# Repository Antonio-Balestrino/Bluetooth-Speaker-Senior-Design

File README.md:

Bluetooth Speaker Senior Design Project:
Welcome to the repository for our senior design group project focused on building a Bluetooth speaker! This project aims to create a portable and versatile Bluetooth speaker system with a focus on high-quality audio output and user-friendly features.

Project Overview:
Our project involves designing and constructing a Bluetooth speaker from scratch. We're incorporating various components including speakers, amplifiers, Bluetooth modules, microcontrollers, and power sources to create a fully functional and aesthetically pleasing speaker system.

Features:
* Bluetooth Connectivity: Seamlessly connect your devices and stream audio wirelessly to the speaker.
* High-Quality Audio: Delivering crisp and clear sound output for an immersive listening experience.
* User-Friendly Interface: Intuitive controls for easy operation, including volume adjustment and playback controls.

Contributors:
Antonio Balestrino​, Blake Chanhmisay​, Rogelio M Hernandez​, Faith Murray​, Tristan Storbeck​

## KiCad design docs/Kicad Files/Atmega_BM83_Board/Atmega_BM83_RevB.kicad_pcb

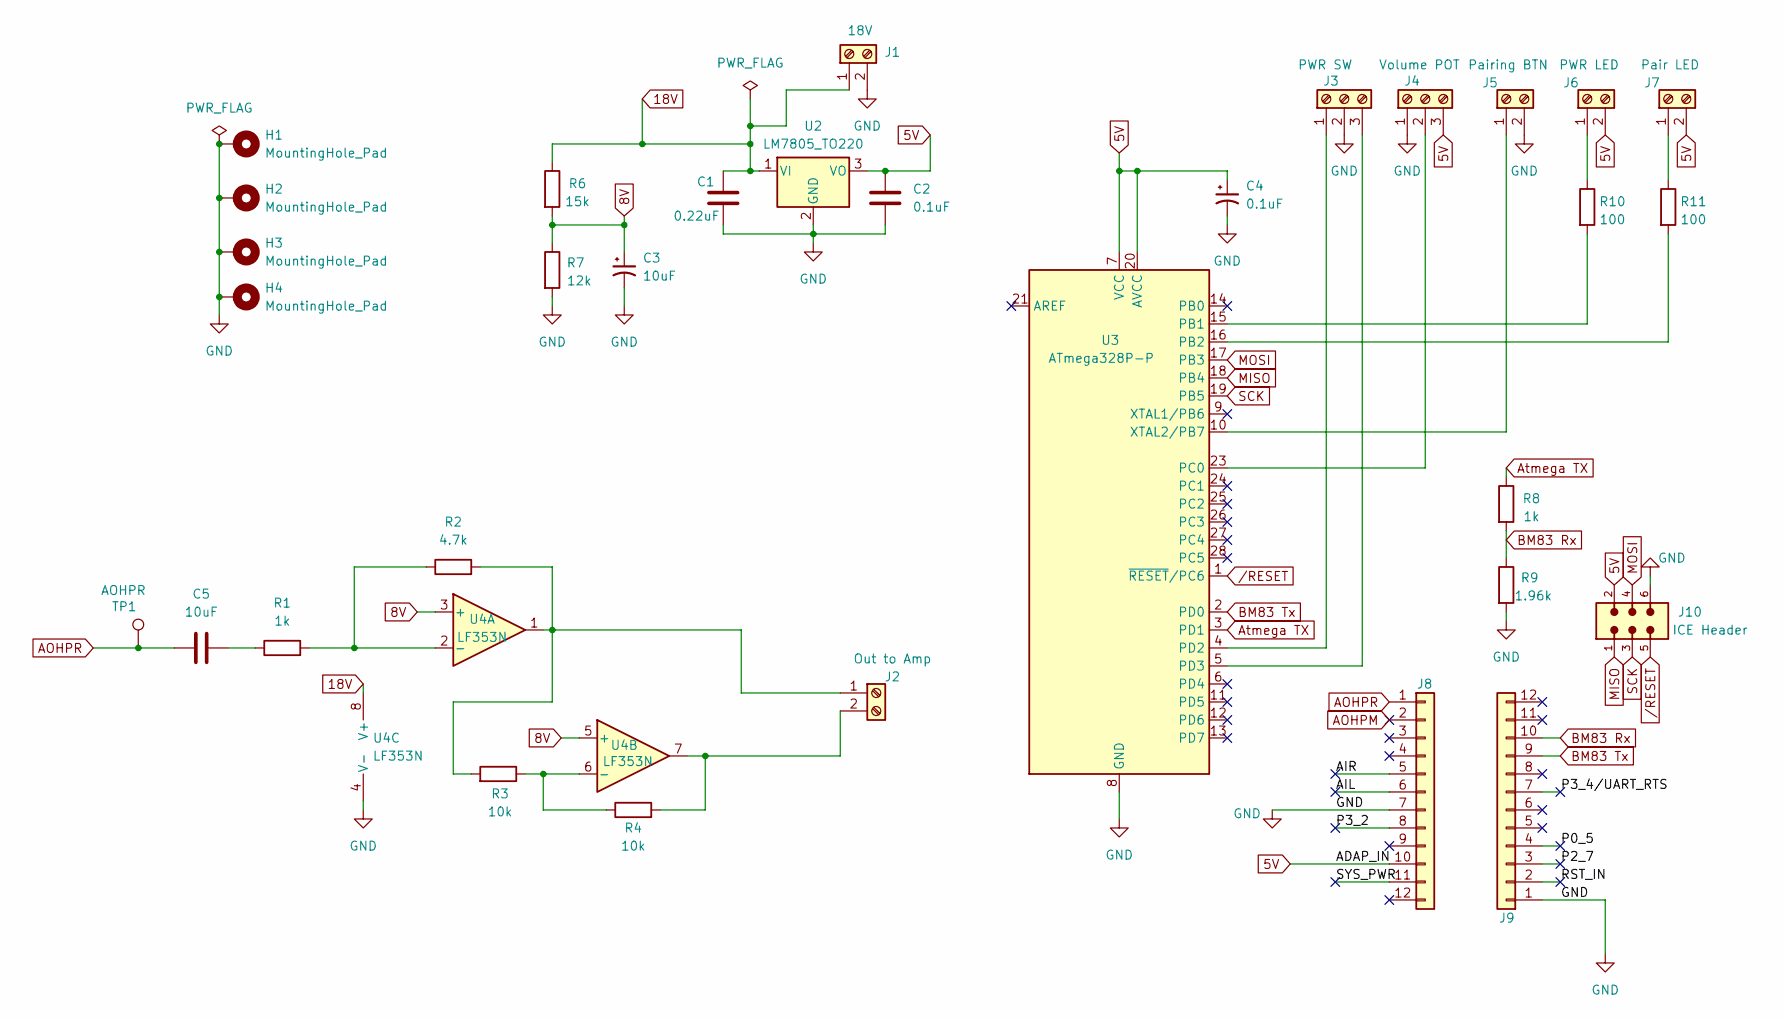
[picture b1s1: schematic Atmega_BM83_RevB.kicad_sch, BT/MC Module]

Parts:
C1: 0.22uF; C_Rect_L7.0mm_W3.5mm_P5.00mm
C2, C4: 0.1uF; C_Rect_L7.0mm_W2.5mm_P5.00mm
C3: 10uF; CP_Radial_Tantal_D5.0mm_P5.00mm
C5: 10uF; C_Disc_D6.0mm_W4.4mm_P5.00mm
H1, H2, H3, H4: MountingHole_Pad; MountingHole_3.5mm_Pad
J1: 18V; TerminalBlock_Phoenix_MKDS-1,5-2_1x02_P5.00mm_Horizontal
J2: Out to Amp; TerminalBlock_Phoenix_MKDS-1,5-2_1x02_P5.00mm_Horizontal
J3: PWR SW; TerminalBlock_Phoenix_MKDS-1,5-3_1x03_P5.00mm_Horizontal
J4: Volume POT; TerminalBlock_Phoenix_MKDS-1,5-3_1x03_P5.00mm_Horizontal
J5: Pairing BTN; TerminalBlock_Phoenix_MKDS-1,5-2_1x02_P5.00mm_Horizontal
J6: PWR LED; TerminalBlock_Phoenix_MKDS-1,5-2_1x02_P5.00mm_Horizontal
J7: Pair LED; TerminalBlock_Phoenix_MKDS-1,5-2_1x02_P5.00mm_Horizontal
J8, J9: Conn_01x12; PinHeader_1x12_P2.54mm_Vertical
J10: ICE Header; ICE_Header; PART-NUMBER 61200621621
R1, R8: 1k; R_Axial_DIN0207_L6.3mm_D2.5mm_P10.16mm_Horizontal
R2: 4.7k; R_Axial_DIN0207_L6.3mm_D2.5mm_P10.16mm_Horizontal
R3, R4: 10k; R_Axial_DIN0207_L6.3mm_D2.5mm_P10.16mm_Horizontal
R6: 15k; R_Axial_DIN0207_L6.3mm_D2.5mm_P10.16mm_Horizontal
R7: 12k; R_Axial_DIN0207_L6.3mm_D2.5mm_P10.16mm_Horizontal
R9: 1.96k; R_Axial_DIN0207_L6.3mm_D2.5mm_P10.16mm_Horizontal
R10, R11: 100; R_Axial_DIN0207_L6.3mm_D2.5mm_P10.16mm_Horizontal
TP1: AOHPR; TestPoint_THTPad_D2.0mm_Drill1.0mm
U2: LM7805_TO220; TO-220-3_Vertical
U3: ATmega328P-P; DIP-28_W7.62mm_LongPads
U4: LF353N; DIP-8_W7.62mm_LongPads

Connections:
5V: C2.1, C4.1, J4.3, J6.2, J7.2, J8.10, J10.2, U2.3 (VO), U3.7 (VCC), U3.20 (AVCC)
8V: C3.1, R6.2, R7.1, U4.3 (+), U4.5 (+)
18V: C1.1, J1.1, R6.1, U2.1 (VI), U4.8 (V+)
/AIL: J8.6
/AIR: J8.5
/P0_5: J9.4
/P2_7: J9.3
/P3_2: J8.8
/P3_4/UART_RTS: J9.7
/RST_IN: J9.2
/SYS_PWR: J8.11
AOHPM: J8.2
AOHPR: C5.1, J8.1, TP1.1
Atmega TX: R8.1, U3.3 (PD1)
BM83 Rx: J9.10, R8.2, R9.1
BM83 Tx: J9.9, U3.2 (PD0)
GND: C1.2, C2.2, C3.2, C4.2, H1.1, H2.1, H3.1, H4.1, J1.2, J3.2, J4.1, J5.2, J8.7, J9.1, J10.6, R7.2, R9.2, U2.2 (GND), U3.8 (GND), U3.22 (GND), U4.4 (V-)
MISO: J10.1, U3.18 (PB4)
MOSI: J10.4, U3.17 (PB3)
unnamed: C5.2, R1.1
unnamed: J2.1, R2.2, R3.2, U4.1
unnamed: J2.2, R4.2, U4.7
unnamed: J3.1, U3.4 (PD2)
unnamed: J3.3, U3.5 (PD3)
unnamed: J4.2, U3.23 (PC0)
unnamed: J5.1, U3.10 (XTAL2/PB7)
unnamed: J6.1, R10.1
unnamed: J7.1, R11.1
unnamed: R10.2, U3.15 (PB1)
unnamed: R11.2, U3.16 (PB2)
unnamed: R1.2, R2.1, U4.2 (-)
unnamed: R3.1, R4.1, U4.6 (-)
SCK: J10.3, U3.19 (PB5)
/RESET: J10.5, U3.1 (~RESET/PC6)

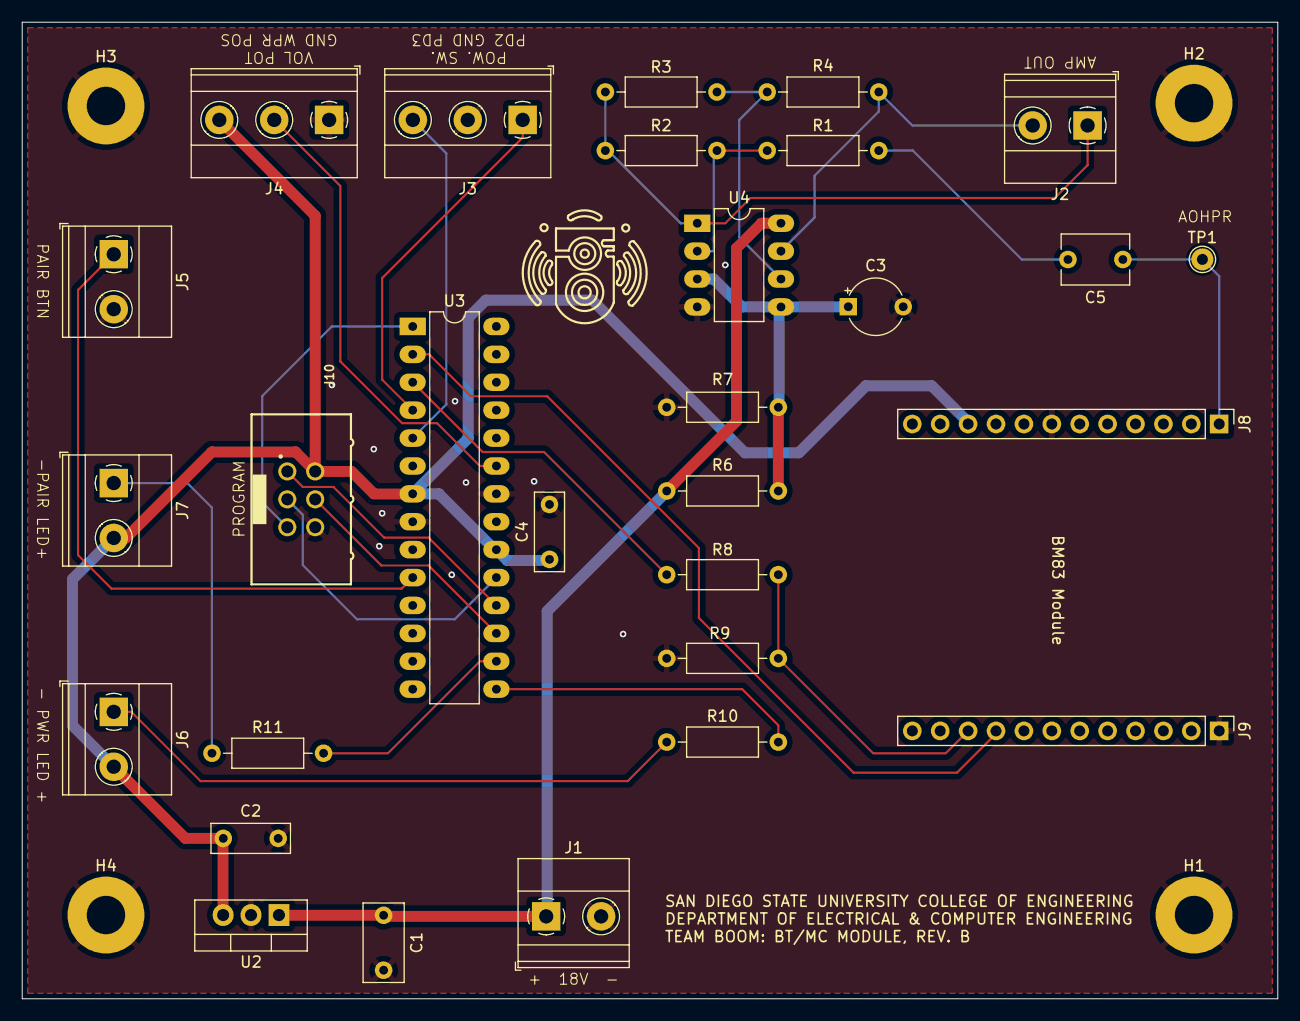
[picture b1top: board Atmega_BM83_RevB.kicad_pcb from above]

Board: 2 copper layers, 114.3 x 88.9 mm, 33 parts (0 on the bottom side), 25 nets.

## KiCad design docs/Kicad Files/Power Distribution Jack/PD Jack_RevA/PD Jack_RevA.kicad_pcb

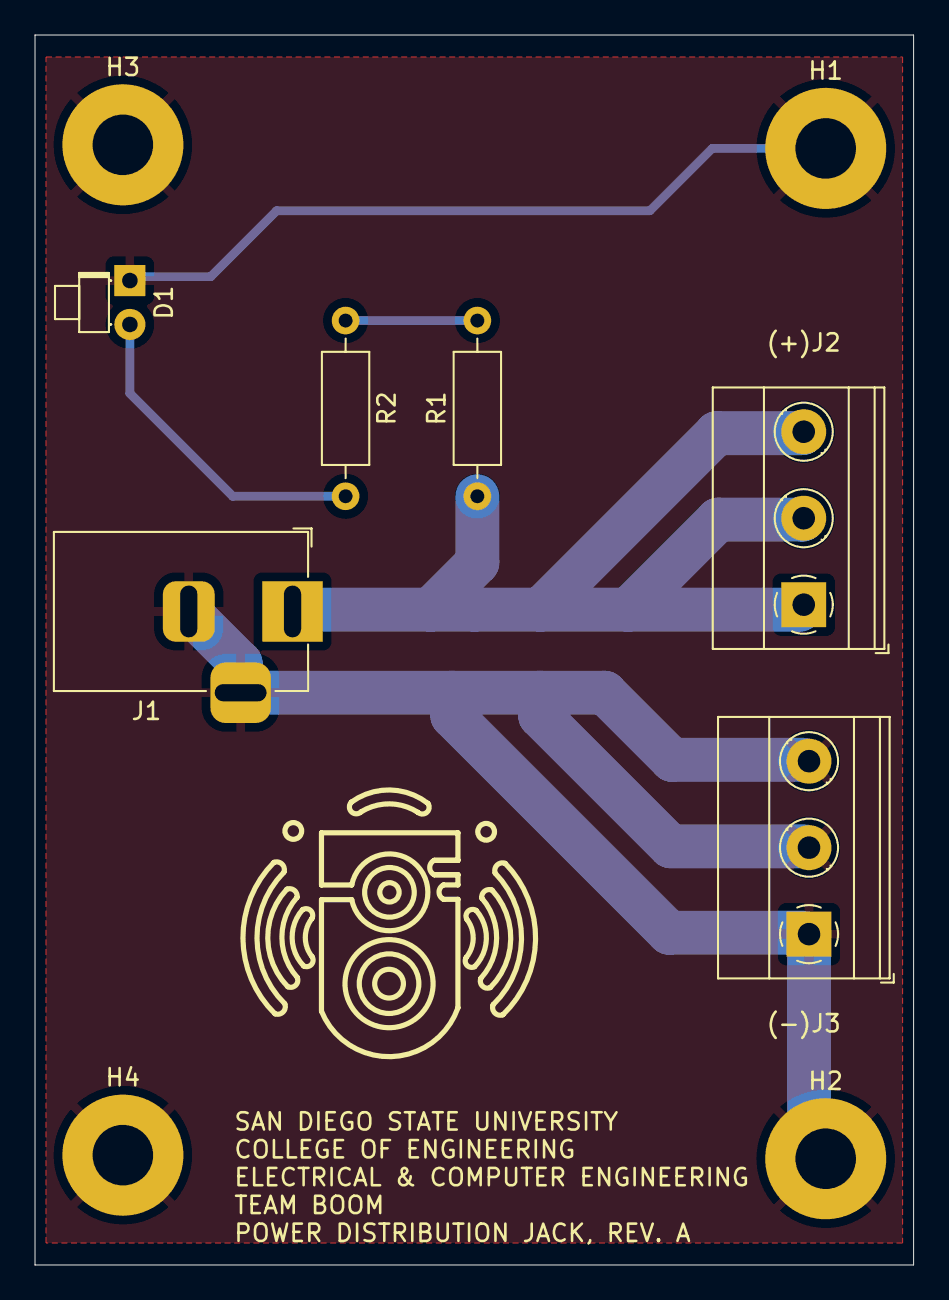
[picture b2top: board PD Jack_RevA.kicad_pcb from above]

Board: 2 copper layers, 50.8 x 71.1 mm, 10 parts (0 on the bottom side), 4 nets.

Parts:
(+)J2: Screw_Terminal_01x03; TerminalBlock_Phoenix_MKDS-1,5-3_1x03_P5.00mm_Horizontal
(-)J3: Screw_Terminal_01x03; TerminalBlock_Phoenix_MKDS-1,5-3_1x03_P5.00mm_Horizontal
D1: LED (PWR Indicator); LED_D1.8mm_W1.8mm_H2.4mm_Horizontal_O1.27mm_Z1.6mm
H1, H2, H3, H4: MountingHole_Pad; MountingHole_3.5mm_Pad
J1: Barrel_Jack_Switch_MountingPin; BarrelJack_Horizontal
R1: 500; R_Axial_DIN0207_L6.3mm_D2.5mm_P10.16mm_Horizontal
R2: 400; R_Axial_DIN0207_L6.3mm_D2.5mm_P10.16mm_Horizontal

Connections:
18V: (+)J2.1, (+)J2.2, (+)J2.3, J1.1, R1.1
GND: (-)J3.1, (-)J3.2, (-)J3.3, D1.1 (K), H1.1, H2.1, H3.1, H4.1, J1.2, J1.3
unnamed: D1.2 (A), R2.2
unnamed: R1.2, R2.1

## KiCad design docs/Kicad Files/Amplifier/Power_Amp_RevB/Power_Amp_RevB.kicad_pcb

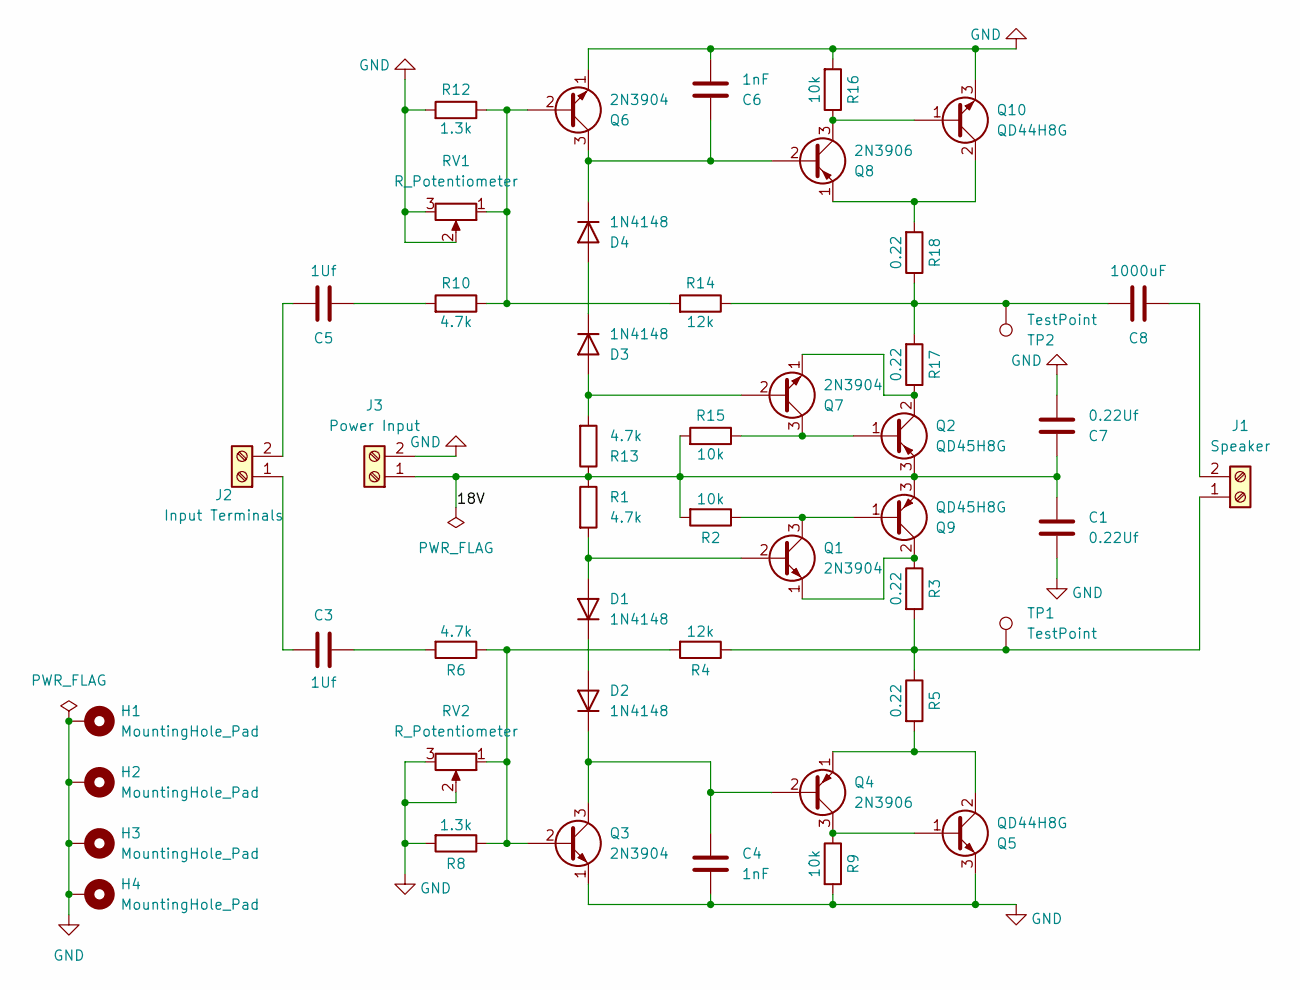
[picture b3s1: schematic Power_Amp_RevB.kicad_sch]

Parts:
C1, C7: 0.22Uf; C_Rect_L7.0mm_W3.5mm_P5.00mm
C3, C5: 1Uf; CP_Radial_D5.0mm_P2.00mm
C4, C6: 1nF; C_Disc_D5.1mm_W3.2mm_P5.00mm
C8: 1000uF; CP_Radial_D12.5mm_P5.00mm
D1, D2, D3, D4: 1N4148; D_DO-41_SOD81_P10.16mm_Horizontal
H1, H2, H3, H4: MountingHole_Pad; MountingHole_3.5mm_Pad
J1: Speaker; TerminalBlock_Phoenix_MKDS-1,5-2_1x02_P5.00mm_Horizontal
J2: Input Terminals; TerminalBlock_Phoenix_MKDS-1,5-2_1x02_P5.00mm_Horizontal
J3: Power Input; TerminalBlock_Phoenix_MKDS-1,5-2_1x02_P5.00mm_Horizontal
Q1, Q3, Q6, Q7: 2N3904; TO-92_Wide
Q2, Q9: QD45H8G; TO-220-3_Vertical
Q4, Q8: 2N3906; TO-92_Wide
Q5, Q10: QD44H8G; TO-220-3_Vertical
R1, R6, R10, R13: 4.7k; R_Axial_DIN0207_L6.3mm_D2.5mm_P10.16mm_Horizontal
R2, R9, R15, R16: 10k; R_Axial_DIN0207_L6.3mm_D2.5mm_P10.16mm_Horizontal
R3, R5, R17, R18: 0.22; R_Axial_DIN0207_L6.3mm_D2.5mm_P10.16mm_Horizontal
R4, R14: 12k; R_Axial_DIN0207_L6.3mm_D2.5mm_P10.16mm_Horizontal
R8, R12: 1.3k; R_Axial_DIN0207_L6.3mm_D2.5mm_P10.16mm_Horizontal
RV1, RV2: R_Potentiometer; Potentiometer_Bourns_3386P_Vertical
TP1, TP2: TestPoint; TestPoint_THTPad_D2.0mm_Drill1.0mm

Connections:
/18V: C1.1, C7.1, J3.1, Q2.3 (E), Q9.3 (E), R1.1, R2.2, R13.1, R15.2
GND: C1.2, C4.2, C6.2, C7.2, H1.1, H2.1, H3.1, H4.1, J3.2, Q3.1 (E), Q5.3 (E), Q6.1 (E), Q10.3 (E), R8.2, R9.2, R12.2, R16.2, RV1.2, RV1.3, RV2.2, RV2.3
unnamed: C3.2, R6.2
unnamed: C5.2, R10.2
unnamed: C8.1, R14.1, R17.2, R18.1, TP2.1
unnamed: D1.2 (A), Q1.2 (B), R1.2
unnamed: D1.1 (K), D2.2 (A)
unnamed: C4.1, D2.1 (K), Q3.3 (C), Q4.2 (B)
unnamed: D3.2 (A), Q7.2 (B), R13.2
unnamed: D3.1 (K), D4.2 (A)
unnamed: C6.1, D4.1 (K), Q6.3 (C), Q8.2 (B)
unnamed: J1.1, R3.2, R4.1, R5.1, TP1.1
unnamed: C8.2, J1.2
unnamed: C3.1, J2.1
unnamed: C5.1, J2.2
unnamed: Q1.3 (C), Q9.1 (B), R2.1
unnamed: Q1.1 (E), Q9.2 (C), R3.1
unnamed: Q2.1 (B), Q7.3 (C), R15.1
unnamed: Q2.2 (C), Q7.1 (E), R17.1
unnamed: Q3.2 (B), R4.2, R6.1, R8.1, RV2.1
unnamed: Q4.3 (C), Q5.1 (B), R9.1
unnamed: Q4.1 (E), Q5.2 (C), R5.2
unnamed: Q6.2 (B), R10.1, R12.1, R14.2, RV1.1
unnamed: Q8.3 (C), Q10.1 (B), R16.1
unnamed: Q8.1 (E), Q10.2 (C), R18.2

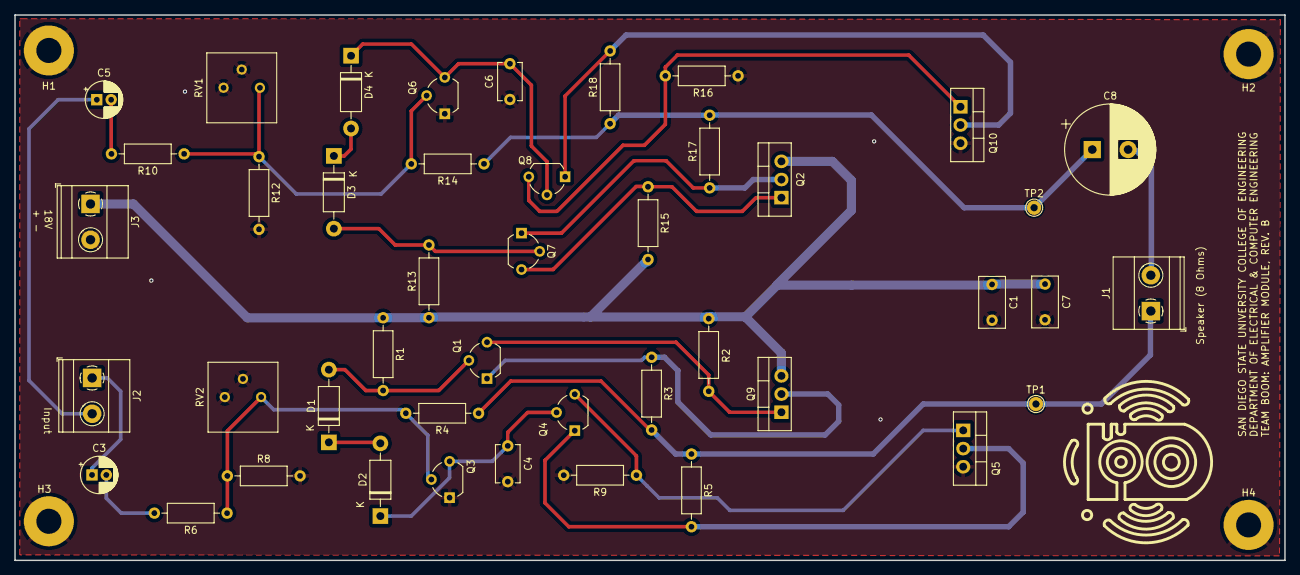
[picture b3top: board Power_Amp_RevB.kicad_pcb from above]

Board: 2 copper layers, 177.4 x 76.2 mm, 48 parts (0 on the bottom side), 25 nets.

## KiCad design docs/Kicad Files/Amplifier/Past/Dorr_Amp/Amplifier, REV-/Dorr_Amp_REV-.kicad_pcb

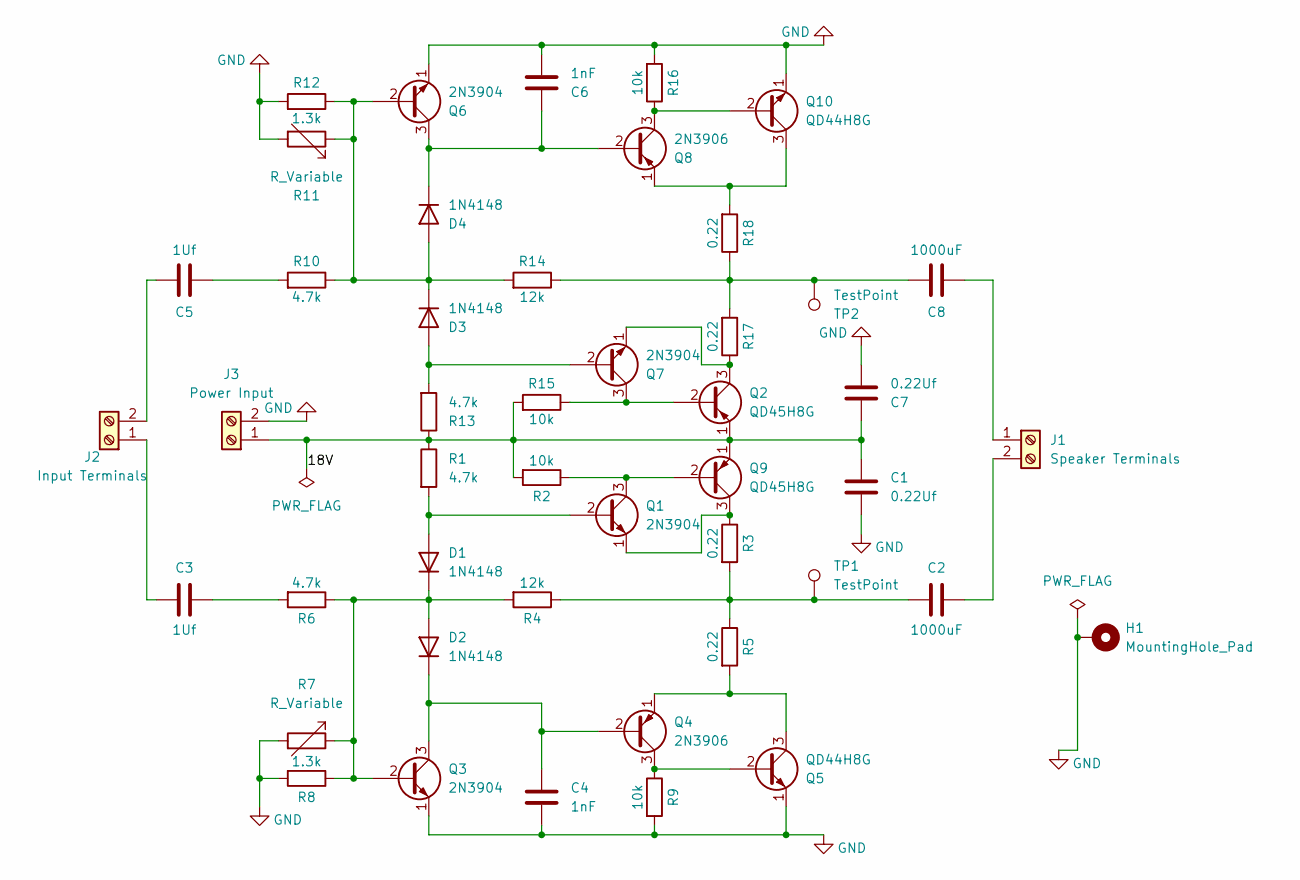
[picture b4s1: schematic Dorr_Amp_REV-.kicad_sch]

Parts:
C1, C7: 0.22Uf; CP_Radial_D4.0mm_P1.50mm
C2, C8: 1000uF; CP_Radial_D12.5mm_P7.50mm
C3, C5: 1Uf; CP_Radial_D4.0mm_P1.50mm
C4, C6: 1nF; CP_Radial_D4.0mm_P1.50mm
D1, D2, D3, D4: 1N4148; D_DO-35_SOD27_P7.62mm_Horizontal
H1: MountingHole_Pad; MountingHole_2.7mm_M2.5_DIN965_Pad
J1: Speaker Terminals; SolderWire-2.5sqmm_1x02_P7.2mm_D2.4mm_OD3.6mm
J2: Input Terminals; SolderWire-2.5sqmm_1x02_P7.2mm_D2.4mm_OD3.6mm
J3: Power Input; SolderWire-2.5sqmm_1x02_P7.2mm_D2.4mm_OD3.6mm
Q1, Q3, Q6, Q7: 2N3904; TO-92_Inline
Q2: QD45H8G; TO-218-3_Vertical
Q4, Q8: 2N3906; TO-92_Inline
Q5: QD44H8G; TO-220-3_Vertical
Q9: QD45H8G; TO-220-3_Vertical
Q10: QD44H8G; TO-218-3_Vertical
R1, R6, R10, R13: 4.7k; R_Axial_DIN0204_L3.6mm_D1.6mm_P5.08mm_Horizontal
R2, R9, R15, R16: 10k; R_Axial_DIN0204_L3.6mm_D1.6mm_P5.08mm_Horizontal
R3, R5, R17, R18: 0.22; R_Axial_DIN0204_L3.6mm_D1.6mm_P5.08mm_Horizontal
R4, R14: 12k; R_Axial_DIN0204_L3.6mm_D1.6mm_P5.08mm_Horizontal
R7, R11: R_Variable; Potentiometer_ACP_CA9-V10_Vertical
R8, R12: 1.3k; R_Axial_DIN0204_L3.6mm_D1.6mm_P5.08mm_Horizontal
TP1, TP2: TestPoint; TestPoint_Loop_D2.50mm_Drill1.0mm

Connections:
/18V: C1.1, C7.1, J3.1, Q2.1 (E), Q9.1 (E), R1.1, R2.2, R13.1, R15.2
GND: C1.2, C4.2, C6.2, C7.2, H1.1, J3.2, Q3.1 (E), Q5.1 (E), Q6.1 (E), Q10.1 (E), R7.2, R8.2, R9.2, R11.2, R12.2, R16.2
unnamed: C2.1, R3.2, R4.1, R5.1, TP1.1
unnamed: C3.2, R6.2
unnamed: C5.2, R10.2
unnamed: C8.1, R14.1, R17.2, R18.1, TP2.1
unnamed: D1.2 (A), Q1.2 (B), R1.2
unnamed: D1.1 (K), D2.2 (A), Q3.2 (B), R4.2, R6.1, R7.1, R8.1
unnamed: C4.1, D2.1 (K), Q3.3 (C), Q4.2 (B)
unnamed: D3.2 (A), Q7.2 (B), R13.2
unnamed: D3.1 (K), D4.2 (A), Q6.2 (B), R10.1, R11.1, R12.1, R14.2
unnamed: C6.1, D4.1 (K), Q6.3 (C), Q8.2 (B)
unnamed: C8.2, J1.1
unnamed: C2.2, J1.2
unnamed: C3.1, J2.1
unnamed: C5.1, J2.2
unnamed: Q1.3 (C), Q9.2 (B), R2.1
unnamed: Q1.1 (E), Q9.3 (C), R3.1
unnamed: Q2.2 (B), Q7.3 (C), R15.1
unnamed: Q2.3 (C), Q7.1 (E), R17.1
unnamed: Q4.3 (C), Q5.2 (B), R9.1
unnamed: Q4.1 (E), Q5.3 (C), R5.2
unnamed: Q8.3 (C), Q10.2 (B), R16.1
unnamed: Q8.1 (E), Q10.3 (C), R18.2

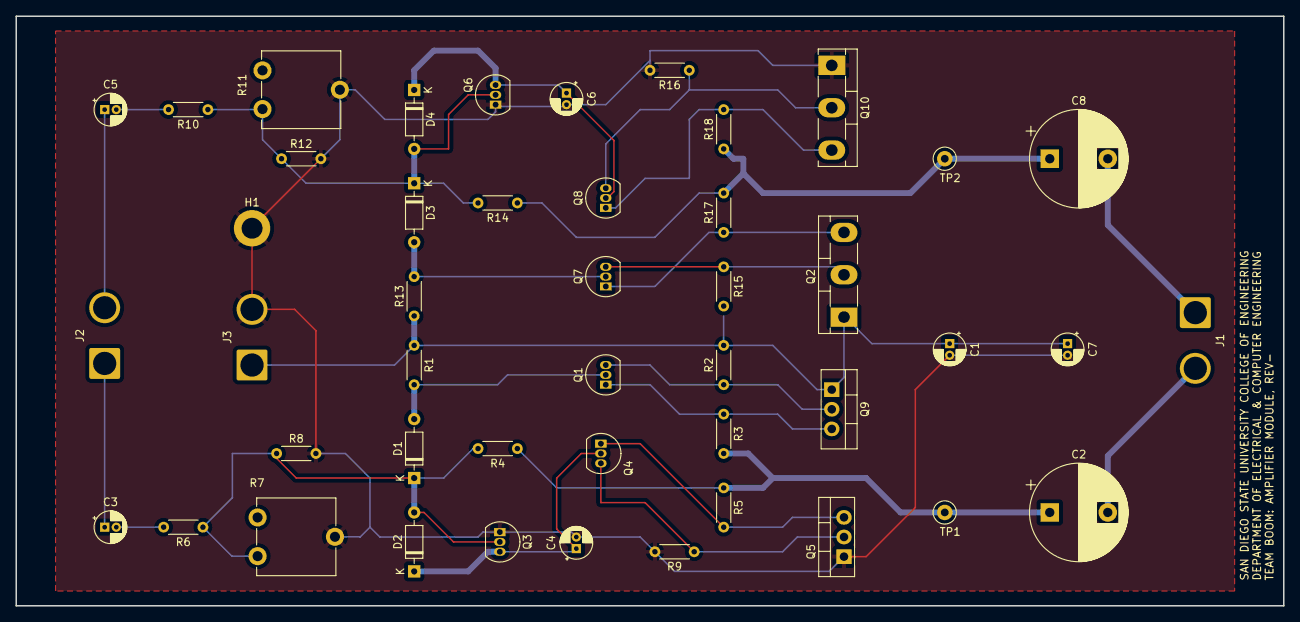
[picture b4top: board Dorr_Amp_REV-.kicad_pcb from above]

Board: 2 copper layers, 163.8 x 76.2 mm, 46 parts (0 on the bottom side), 24 nets.

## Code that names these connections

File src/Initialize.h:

// Initialize.h
#ifndef INITIALIZE_H
#define INITIALIZE_H

#include <avr/io.h>

#define POWER_ON_PIN PD2
#define POWER_OFF_PIN PD3
#define LED_POWER_PIN PB1
#define BUTTON_PIN PB7


void Power_Init(void);
void ADC_Init(void);
uint16_t ADC_Read(void);
void turn_on_LED(void);
void turn_off_LED(void);

#endif

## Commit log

2024-08-29 Create Parts List
2024-08-29 Critical Design Review Presentation
2024-08-30 Final Report for first semester
2024-08-30 Create State Diegrams
2024-08-30 State Diagrams of speaker system
2024-08-30 Detailed Diagram of current parts
2024-08-30 Breadboard Schematic of atmel ice, mc, and bm
2024-08-30 Create bm83_code
2024-08-30 C code for bm83 micocontroller
2024-09-10 Added Kicad and LTSpice files
    Added directories for LTSpice and Kicad to maintain current versions of schematics and PCB designs
2024-09-11 Amp Board Update
    Updated the power transistor pins in the schematic to reflect datasheets. Minor changes to component placement.
2024-09-11 Updated REV-A to REV-
2024-09-12 Fixed all footprints
    All footprints should be good. Need to double check the capacitor lead spacing with those in the lab.
2024-09-12 Added datasheets for amp parts
2024-09-12 All footprints verified
2024-09-12 removed (most) old traces
2024-09-12 Updated current flow PDF
2024-09-17 Amplifier Rev- Updates
    Traces have been added to Amplifier Rev-, components were moved/shifter slightly to allow no interferences.
2024-09-17 PCB traces updated - waiting feedback from Mark
2024-09-17 cleaned up amp directory
2024-09-18 made changes per Mark's suggestions
2024-09-18 Rev A files
    first Amplifier prototype shall be referred to as RevA
2024-09-18 no more v1.0
    removed/renamed all instances of v1.0 as RevA
2024-09-18 Rev A zip folder renamed
2024-09-18 changed some footprints per Mark
    -routed input traces to back of PCB
    -changed footprints of pots and terminal blocks
    -flipped terminal blocks so orientation is correct
    -added terminal block descriptions
2024-09-18 re-generated gerber files
2024-09-21 added c file for volume module
2024-09-21 Created module for pairing button
2024-09-24 Create Power management module
    This module contains two interrupts, both triggered on rising edge. One interrupt is for power down and one is for power on. These interrupts change the currentState that controls when the system is 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
2024-09-25 Added BM83 Carrier Board to Kicad Directory
2024-09-25 Started BM83/Atmega
2024-09-25 Minor changes to BM83/Atmega board
2024-09-26 Added voltage divider
2024-09-27 Updated pairing_button.c
2024-09-29 updates for BM83/Atmega schematic
2024-09-30 more work on BM83/Atmega schematic
2024-10-02 Updated REF-DES on Amp LTSpice model to match Amp PCB
2024-10-02 Update to last push
2024-10-02 minor changes to amp LTSPice model
2024-10-02 updated main.c
2024-10-02 more work on Atmega/BM83 schematic
2024-10-03 Latest version of power module.
    This module turns on the BM83, but doesn't power it down. Need to do some debugging to see what is being sent to the BM83
2024-10-03 Updated power module
    Commented out MFB commands because we didn't need it in prototype. Changed interrupts to trigger on rising and falling edges instead of on low state.
2024-10-04 changes to power amp RevB
2024-10-04 added event storage and acknowledge function
2024-10-04 Completed power_management module
    Interrupts now both trigger on rising edge. Added some debounce logic with a delay
2024-10-04 Paired to phone and renamed Blake's code
2024-10-07 got rid of unec. LTSpice schematics
2024-10-07 updates to BM83/MC schematic
2024-10-08 Kicad autobackups
2024-10-08 volume op codes done
2024-10-08 added scope captures
2024-10-09 added ICE header and other connections to BM83/MC schematic
2024-10-10 op-amp changes to MC/BM83 schematic
2024-10-11 all footprints assigned BM83/Atmega schematic
2024-10-12 changed volume switch and removed powerMFB
2024-10-12 final changes to BM83/Atmega schematic
2024-10-13 Rev B Update
    This update on 10/12/2024 includes a refreshed Amplifier Rev.B design along with a longer PCB length along with courtyards for the power transistors and a logo on the board. AutoCAD .dxf files have b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
2024-10-13 initial trace routing for MC/BM83 PCB complete
2024-10-13 BT/MC PCB redesign. rerouted traces. awaiting QA inspection
2024-10-13 final changes to both PCBs before review
2024-10-13 BT/MC Module
    added logo to new BT/MC board and added a reference schematic to data sheets folder
2024-10-13 simulated lab test environments
2024-10-13 generated drill files and plots
2024-10-14 gerber files generated
2024-10-14 No more events, just pairs
2024-10-14 widened traces per Mark's suggestion. connected AVCC and C7 as per datasheet.
2024-10-14 excluded an error from the ERC
2024-10-14 Organized code into .h and .c files
    Separated code into 5 header files: Globals.h, USART.h, Initialize.h, Commands.h, Interrupts.h
2024-10-15 BM83-Atmega Schematic
    moved the schematic to the diagrams folder
2024-10-16 current and power calculations for wiring
2024-10-18 AutoCAD
    includes AutoCAD drawing
2024-10-18 Pending BOMs
    xls files for current BOMs
2024-10-18 kicad autobackup
2024-10-19 Enclosure DWG & BOMs
2024-10-23 updated initialize.h and interrupts.c
    In initialize I changed the power LED to PB1 from PB5. In interrupts I switched the interrupts in which turn on/off functions were in. Switched turn on from INT0 to INT1 and vice versa for turn off
2024-10-24 minor ref des changes
2024-10-24 soldering update
2024-11-08 AutoCAD & THD Scopes
2024-11-12 PD Jack Files - initial design
    Created a Power Distribution block on KiCAD. It is an initial design and will be given the status of RevA once finalized.
2024-11-12 No real changes to MC-BT board, just backups upload
2024-11-12 New Updates to PD Jack
2024-11-12 PD Jack_RevA
2024-11-12 footprint edit - not complete
2024-11-13 PD_Jack Rev A (again)
2024-11-13 scope captures
2024-11-13 archived old PD Jack revisions. current revision is RevB
2024-11-14 updated BT/MC board to reflect changes: removed C2 and C3, changed some cap locations
2024-11-14 renamed current rev to RevB
2024-11-15 THD Calculation Matlab file added
2024-11-15 added pics directory
2024-12-02 PD Jack & AutoCAD
2024-12-02 Name Plate Files
2024-12-08 cropped DC board pic
